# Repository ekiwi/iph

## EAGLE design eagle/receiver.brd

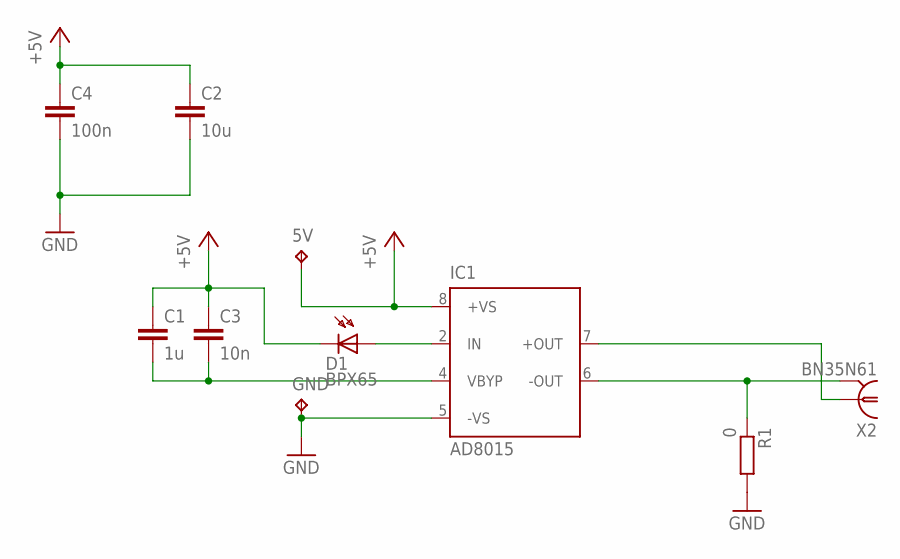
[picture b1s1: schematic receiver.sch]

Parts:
5V: TPTP20SQ; TP20SQ
C1: 1u; C1206
C2: 10u; C1206
C3: 10n; C0603
C4: 100n; C0603
D1: BPX65
GND: TPTP20SQ; TP20SQ
IC1: AD8015; SO8
R1: 0; R1206
X2: BN35N61; B35N61

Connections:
+5V: 5V.TP, C1.1, C2.1, C3.1, C4.1, D1.K (C), IC1.8 (+VS)
GND: C2.2, C4.2, GND.TP, IC1.5 (-VS), R1.2
unnamed: C1.2, C3.2, IC1.4 (VBYP)
unnamed: IC1.7 (+OUT), X2.1
unnamed: IC1.6 (-OUT), R1.1, X2.2, X2.3 (2), X2.4 (2), X2.5 (2)
unnamed: D1.A, IC1.2 (IN)

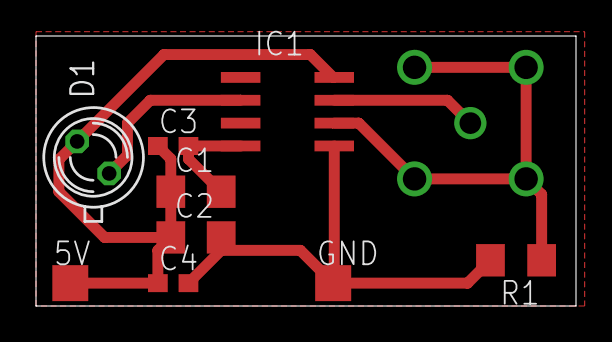
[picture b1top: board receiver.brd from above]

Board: 2 copper layers, 30.0 x 15.0 mm, 10 parts (1 on the bottom side), 6 nets.

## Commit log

2014-06-10 Spice: add simiulation sources
2014-06-10 Spice: add signal source file
2014-06-10 Measurements: add data
2014-06-10 Add Todo
2014-06-10 Add log file
2014-06-10 New measurements.
2014-06-10 Pyhon: add demodulator
2014-06-10 Stm32: source for lcd transmitter
2014-06-10 AC coupling on measurement results
2014-06-10 Measurement: 3Hz with comparator on output
2014-06-10 Measurements: screenshot of computed demodulation
2014-06-10 Log: update
2014-06-11 Move hamming functions to separate file.
2014-06-11 Lcd Link: uart output working
2014-06-11 Tx: let's just reimplement UART ...
2014-06-11 Added Hamming::decode() method + some testing
2014-06-11 Fix previous commit
2014-06-11 Change names of settings around
2014-06-11 Receiver source
2014-06-11 Added some debug output in Hamming::decode()
2014-06-11 New measurements added
2014-06-20 Added receiver schematics / board layout
2014-07-10 Transmitter: MSB first
2014-07-10 Receiver: toggle pin when sampling
2014-07-10 Measurements: Receiver logs
2014-07-10 Latest LCD Transmitter Code
2014-07-10 20MHz Data Transmission
2014-07-10 Log: 3rd and 10th of July
2014-07-10 Measurements: 2014-07-03
2014-07-10 Wow! Such diagrams, much eye, very Mbits!
2014-07-12 Add photos and presentation
2014-07-12 Improve sweep document
2014-07-12 Presentation: add more slides
2014-07-12 Audacity-Schmarrn
2014-07-16 Fixed some of the pictures and charts in the presentation... (Still not sure about pictures on slide 4 and especially 7?)
2014-07-16 Nein
2014-07-16 This is a useful commit message about what was changed in the presentation
2014-07-16 Spice/Presentation: add modulated current source
2014-07-16 Converted the two plots into a .png file to make Impress happy
2014-07-16 Corrected some folder names (mainly to try out git mv...)
2014-07-16 Presentation: add software UART
2014-07-16 Cosmetic changes
2014-07-17 UART: add data format
2014-07-17 UART: fix pie chart
2014-08-03 Report: add very basic latex document
2014-08-03 Final version of the sweep spreadsheet
2014-08-04 Vorschlag für eine Gliederung Ignoriere .dvi-Files (irgendetwas automatisch generiertes)
2014-08-14 report: add some bullet points
2014-08-14 report: describe direct modulation transmitter
2014-08-14 report: Started writing out the sections 2 / 2.1
2014-08-14 report: eye diagrams
2014-08-14 report: Added a basic LCD frequency response plot
2014-08-14 report: some plot formatting changes
2014-08-14 One more fix
2014-08-14 report: digital receiver
2014-08-14 report: use siunitx package
2014-08-29 Small diagram changes
2014-08-29 Report: add receiver schematic
2014-08-29 Report: add pdfs
2014-08-29 Report: add section about ad0815
2014-08-29 Report: add direkt modulation results
2014-08-29 Completed section 2.1.1
2014-08-29 Report: Appendix: add code listings
2014-08-29 Began working on section 2.2
2014-08-29 Add pgf-pie package
2014-08-29 Report: add UART figures
2014-08-29 Finished section 2.2
2014-08-29 Fix broken merge
2014-08-29 Report: add software uart signal chain
2014-08-29 Some small improvements of 2.1.1
2014-08-29 Report: started chapter on digital transmission
2014-08-29 Added IPH logo + a strange introduction
2014-08-30 Added photo of the experiment setup to section 2.2
2014-08-30 Report: finish digital data tx section
2014-08-30 Report: footnotes are great
2014-08-30 Report: add conclusion
2014-08-30 Report: add custom titlepage
2014-08-30 Report: Fixed footnote hyperlinks, some title page formatting changes
2014-08-30 Report: Some corrections / completions / language fixes
2014-08-30 Report: Gone through the first half of the text
2014-08-31 Report: done (hopefully)
2014-08-31 Report: add final pdf
